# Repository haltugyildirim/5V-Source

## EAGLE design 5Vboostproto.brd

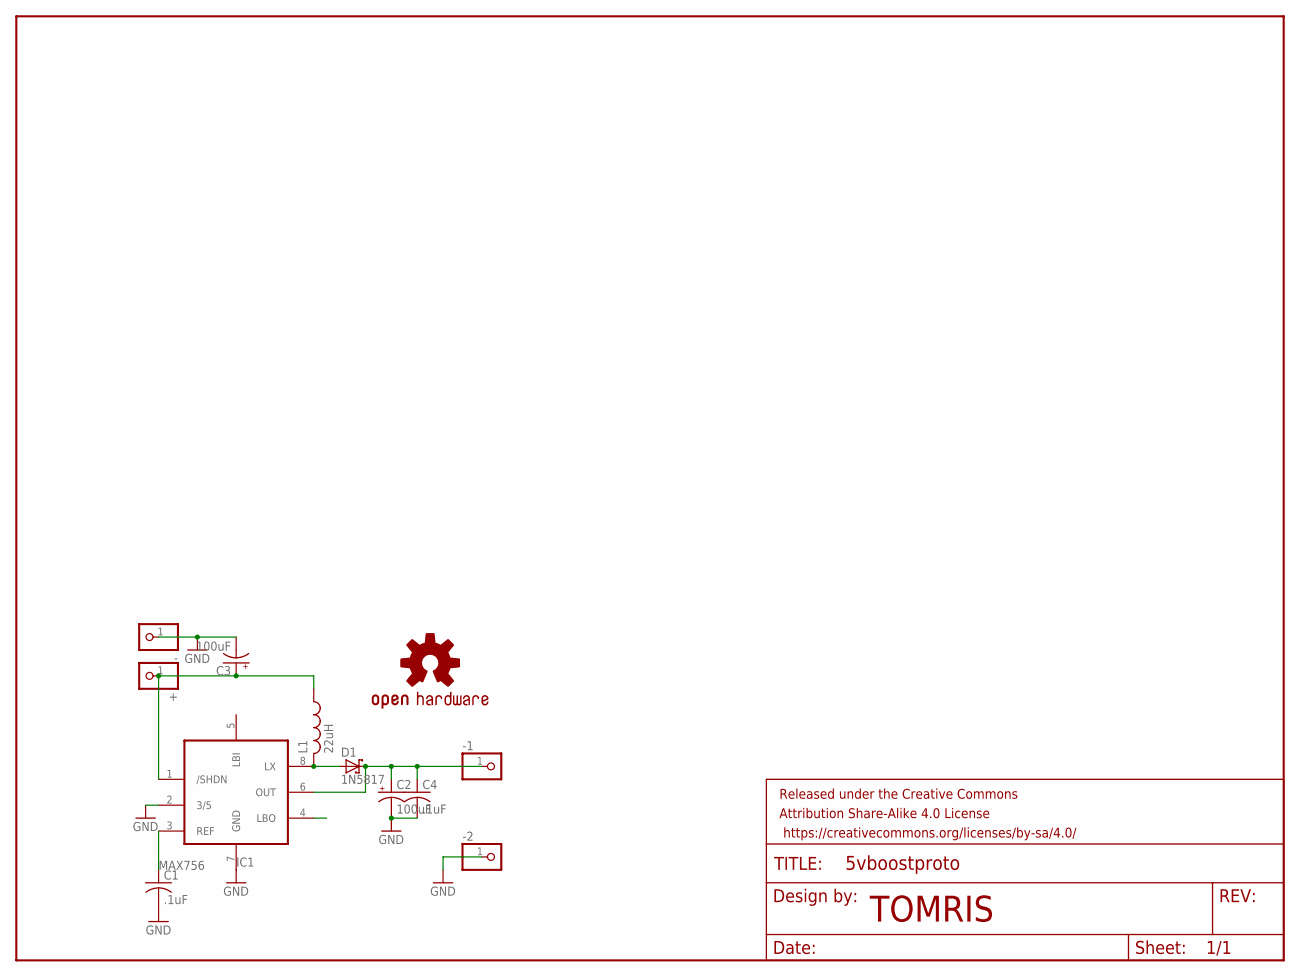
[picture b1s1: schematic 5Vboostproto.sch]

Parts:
+: PINHD-1X1; 1X01
-, -1, -2: PINHD-1X1; 1X01
C1, C4: .1uF; C025-024X044
C2, C3: 100uF; E2,5-5
D1: 1N5817; DO41-10
FRAME1: FRAME-LETTER; CREATIVE_COMMONS
IC1: MAX756; DIL08
L1: 22uH; 2747
LOGO1: OSHW-LOGOM; OSHW-LOGO-M

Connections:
GND: -.1, -2.1, C1.2, C2.-, C3.-, C4.2, IC1.2 (3/5), IC1.7 (GND)
unnamed: C1.1, IC1.3 (REF)
unnamed: +.1, C3.+, IC1.1 (/SHDN), L1.P$1 (1)
unnamed: -1.1, C2.+, C4.1, D1.C, IC1.6 (OUT)
unnamed: D1.A, IC1.8 (LX), L1.P$2 (2)

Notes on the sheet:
TOMRIS

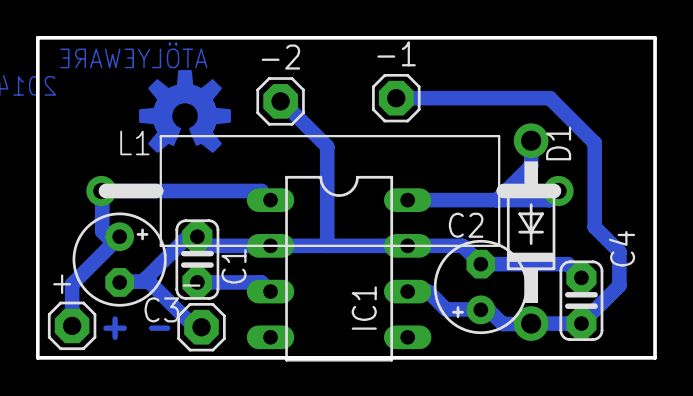
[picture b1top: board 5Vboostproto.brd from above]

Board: 2 copper layers, 34.3 x 17.8 mm, 13 parts (0 on the bottom side), 5 nets.

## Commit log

2016-08-26 add initial design files
    add files

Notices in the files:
parts and their libraries:
OSHW-LOGO-M-BOTTOMCOP: Licensing: Creative Commons ShareAlike 4.0 International - https://creativecommons.org/licenses/by-sa/4.0
SparkFun-Aesthetics: Released under the Creative Commons Attribution Share-Alike 4.0 License
SparkFun-Aesthetics: https://creativecommons.org/licenses/by-sa/4.0
